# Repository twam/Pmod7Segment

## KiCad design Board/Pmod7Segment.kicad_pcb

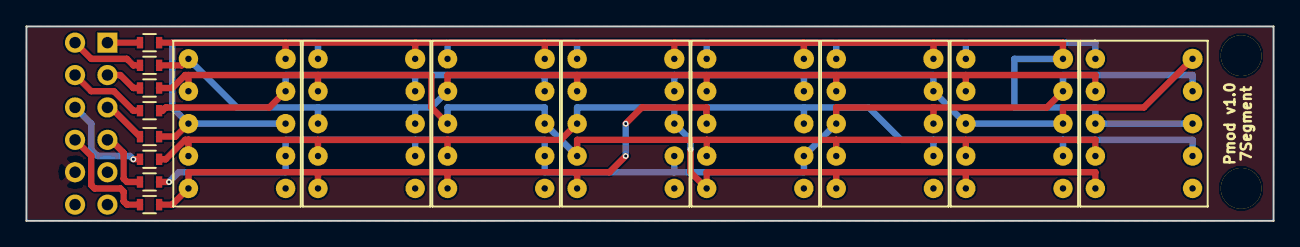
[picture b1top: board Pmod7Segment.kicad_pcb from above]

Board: 2 copper layers, 97.8 x 15.2 mm, 19 parts (0 on the bottom side), 17 nets.

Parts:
J1: PMOD; PMOD-DUAL-MALE
LED1, LED2, LED3, LED4, LED5, LED6, LED7, LED8: SA39-11
MOUNTING_HOLE_3-2MM_M3, MOUNTING_HOLE_3-2MM_M3#2: VAL**; MOUNTING_HOLE_3-2MM_M3
R1, R2, R3, R4, R5, R6, R7, R8: R; R_0603

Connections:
/S0: LED1.10, LED2.10, LED3.10, LED4.10, LED5.10, LED6.10, LED7.10, LED8.3, LED8.8, R1.2
/S1: LED1.9, LED2.9, LED3.9, LED4.9, LED5.9, LED6.9, LED7.3, LED7.8, LED8.10, R6.1
/S2: LED1.7, LED2.7, LED3.7, LED4.7, LED5.7, LED6.3, LED6.8, LED7.9, LED8.9, R4.2
/S3: LED1.5, LED2.5, LED3.5, LED4.5, LED5.3, LED5.8, LED6.7, LED7.7, LED8.7, R8.1
/S4: LED1.4, LED2.4, LED3.4, LED4.3, LED4.8, LED5.5, LED6.5, LED7.5, LED8.5, R7.1
/S5: LED1.2, LED2.2, LED3.3, LED3.8, LED4.4, LED5.4, LED6.4, LED7.4, LED8.4, R2.2
/S6: LED1.1, LED2.3, LED2.8, LED3.2, LED4.2, LED5.2, LED6.2, LED7.2, LED8.2, R5.1
/S7: LED1.3, LED1.8, LED2.1, LED3.1, LED4.1, LED5.1, LED6.1, LED7.1, LED8.1, R3.2
GND: J1.5, J1.11
unnamed: J1.1, R1.1
unnamed: J1.2, R2.1
unnamed: J1.3, R3.1
unnamed: J1.4, R4.1
unnamed: J1.7, R5.2
unnamed: J1.8, R6.2
unnamed: J1.9, R7.2
unnamed: J1.10, R8.2

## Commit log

2015-01-22 Initial commit with board files
2015-01-24 FPGA Source Files
2019-01-05 Add Verilog example
